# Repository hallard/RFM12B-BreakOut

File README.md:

RFM12B RFM69CW breakout board NRF24L01 socket
=============================================

This is a utility breakout board for connecting RFM12B or RFM69CW device onto 
NRF24L01 sockets

this breakout add the feature of one of : 
- **adding** Micro SD card connector (V1.1 only)
- **adding** SPI Flash EEProm
- **adding** Some Leds to see what's going on

The 1.2 version has been added to be smaller than the 1.1 version, to achieve this I needed 
to remove the SD Card holder, so if you want SD use version 1.1.

1.2 version comes in two versions, one with classic 2x4 PTH connector and the other with the same
but SMD version of the connector, this permit to have the PCB quite the same size of the original
RFM12B or RFM69CM module size.

This has been created to work with the [ArduiPi][4] Project, but this breakout
can be used anywhere where you use NRF24L01 or has NRF24L01 connector.

The same breakout board exists also for RFM69W and RFM69HW on this [repo][2]
 
ArduiPi project is a shield for Raspberry Pi that brings Arduino low level extended I/O to Raspberry Pi.

You can find information about this project and others on [ArduiPi Site][4] 

Check out news and other on my [blog][5]

Detailed Description
====================

Everything is documented on this dedicated [post][6]

# **Version 1.2**  

## Schematic  

## Boards  
&nbsp;
&nbsp;

# **Version 1.2 SMD connector**  

## Schematic  
  
## Boards  
&nbsp;
&nbsp;

# **Version 1.1 with SD Card**  

## Schematic  
  
## Boards  
&nbsp;
&nbsp;

[2]: [https://github.com/hallard/RFM69W-BreakOut]
[3]: http://hallard.me/rfm12b-breakout/ 
[4]: http://hallard.me/arduipi
[5]: http://hallard.me
[6]: http://hallard.me/rfm12b-breakout/

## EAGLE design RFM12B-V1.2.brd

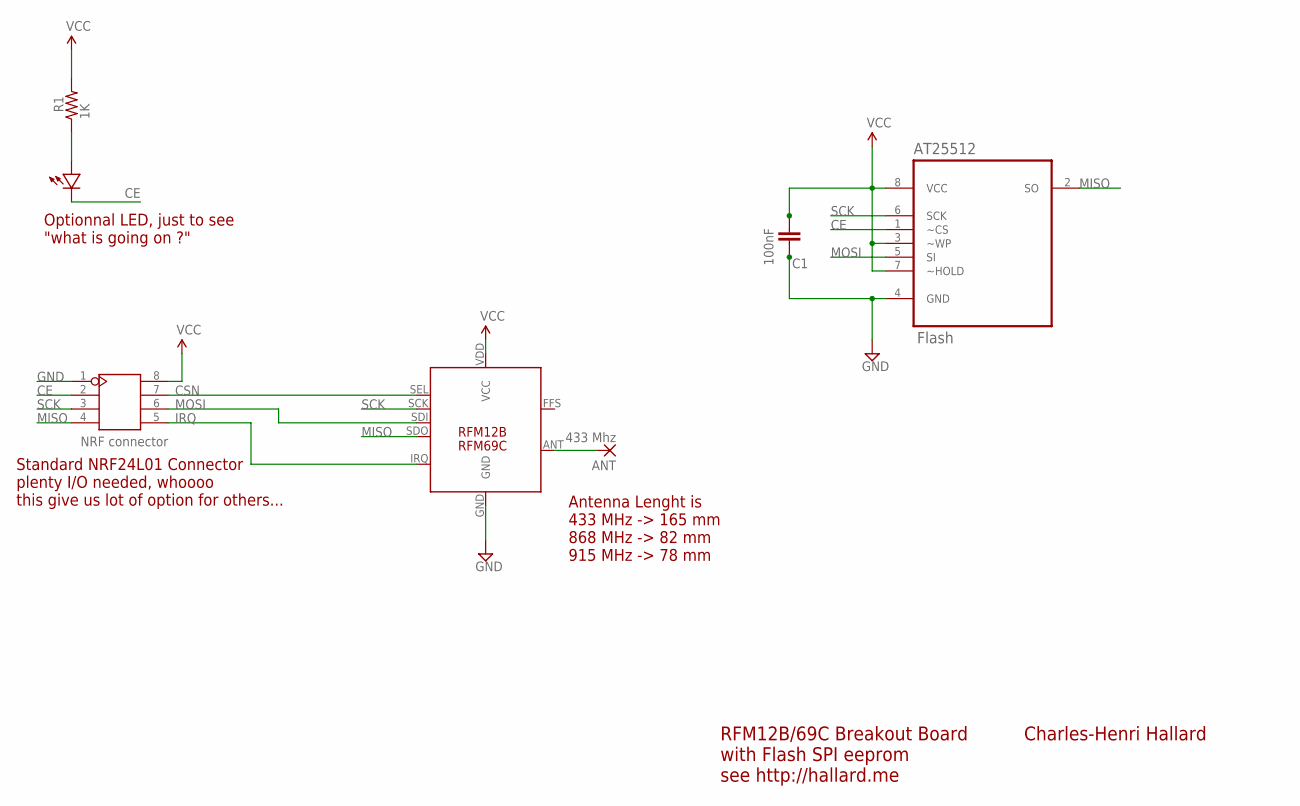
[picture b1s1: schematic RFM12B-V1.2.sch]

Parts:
ANT: 433 Mhz; 1,6/0,8
AT25512: Flash; SOIC127P600X175-8N
C1: 100nF; 0805-CAP
J1: NRF connector; 2X4P-2.54
R1: 1K; 0805-RES
U$1: LED0805-LARGE; 0805-LED-LARGEPADS
U$2: RFM12B

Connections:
CE: AT25512.1 (~CS), J1.2, U$1.MINUS
CSN: J1.7, U$2.SEL
GND: AT25512.4 (GND), C1.2, J1.1, U$2.GND
IRQ: J1.5, U$2.IRQ
MISO: AT25512.2 (SO), J1.4, U$2.SDO
MOSI: AT25512.5 (SI), J1.6, U$2.SDI
unnamed: ANT.1, U$2.ANT
unnamed: R1.1, U$1.PLUS
SCK: AT25512.6 (SCK), J1.3, U$2.SCK
VCC: AT25512.3 (~WP), AT25512.7 (~HOLD), AT25512.8 (VCC), C1.1, J1.8, R1.2, U$2.VDD (VCC)

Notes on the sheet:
RFM12B/69C Breakout Board with Flash SPI eeprom see http://hallard.me
Charles-Henri Hallard
Antenna Lenght is 433 MHz -> 165 mm 868 MHz -> 82 mm 915 MHz -> 78 mm
Optionnal LED, just to see "what is going on ?"
Standard NRF24L01 Connector plenty I/O needed, whoooo this give us lot of option for others...
RFM69C

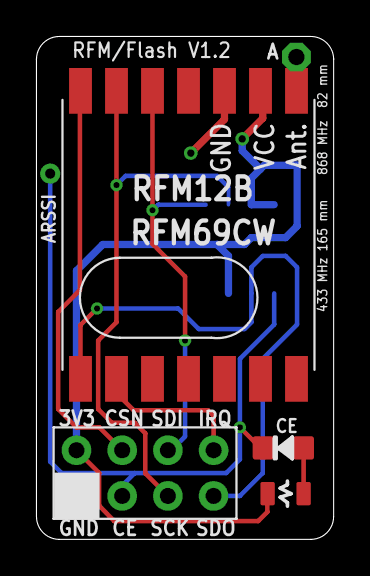
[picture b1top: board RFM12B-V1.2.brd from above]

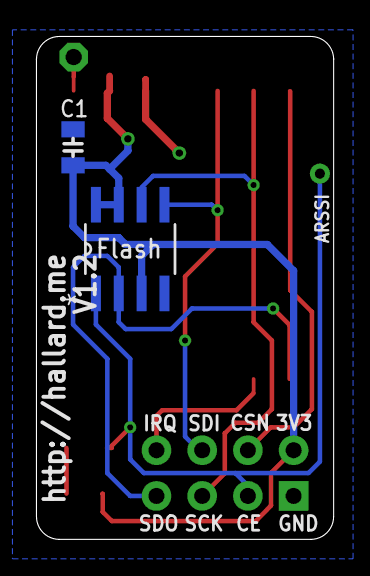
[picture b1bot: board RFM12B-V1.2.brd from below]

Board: 2 copper layers, 16.5 x 27.9 mm, 7 parts (2 on the bottom side), 10 nets.

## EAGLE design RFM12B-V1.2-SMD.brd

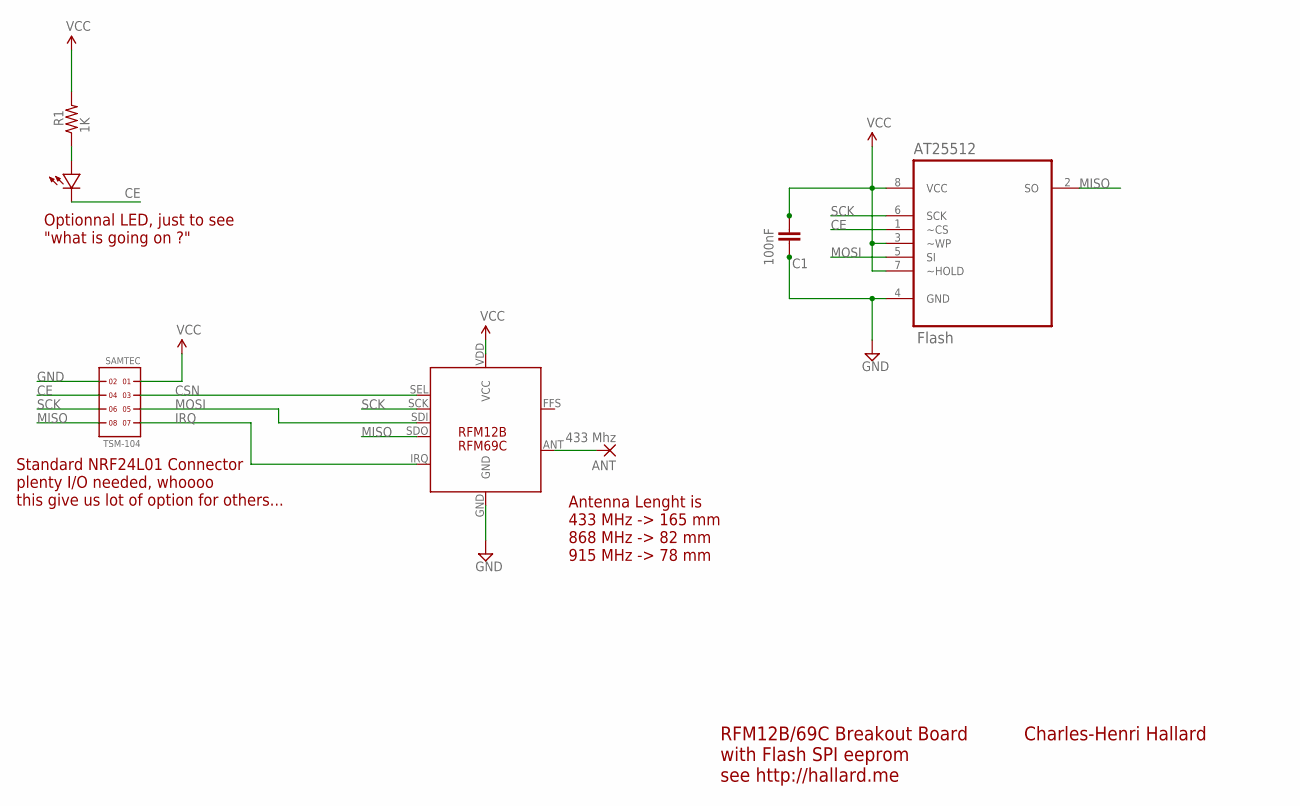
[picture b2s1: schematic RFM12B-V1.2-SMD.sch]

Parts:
ANT: 433 Mhz; 1,6/0,8
AT25512: Flash; SOIC127P600X175-8N
C1: 100nF; 0805-CAP
R1: 1K; 0805-RES
SAMTEC: TSM-104
U$2: RFM12B
U$3: LED0805-LARGE; 0805-LED-LARGEPADS

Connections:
CE: AT25512.1 (~CS), SAMTEC.4, U$3.MINUS
CSN: SAMTEC.3, U$2.SEL
GND: AT25512.4 (GND), C1.2, SAMTEC.2, U$2.GND
IRQ: SAMTEC.7, U$2.IRQ
MISO: AT25512.2 (SO), SAMTEC.8, U$2.SDO
MOSI: AT25512.5 (SI), SAMTEC.5, U$2.SDI
unnamed: ANT.1, U$2.ANT
unnamed: R1.1, U$3.PLUS
SCK: AT25512.6 (SCK), SAMTEC.6, U$2.SCK
VCC: AT25512.3 (~WP), AT25512.7 (~HOLD), AT25512.8 (VCC), C1.1, R1.2, SAMTEC.1, U$2.VDD (VCC)

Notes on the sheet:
RFM12B/69C Breakout Board with Flash SPI eeprom see http://hallard.me
Charles-Henri Hallard
Antenna Lenght is 433 MHz -> 165 mm 868 MHz -> 82 mm 915 MHz -> 78 mm
Optionnal LED, just to see "what is going on ?"
Standard NRF24L01 Connector plenty I/O needed, whoooo this give us lot of option for others...
RFM69C

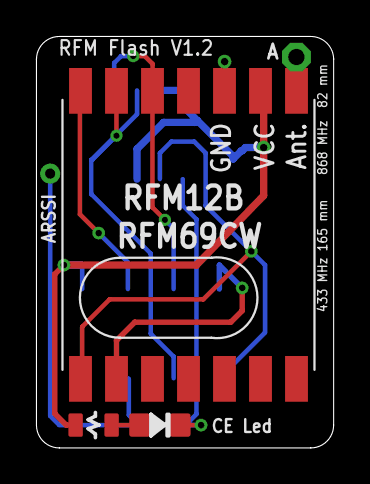
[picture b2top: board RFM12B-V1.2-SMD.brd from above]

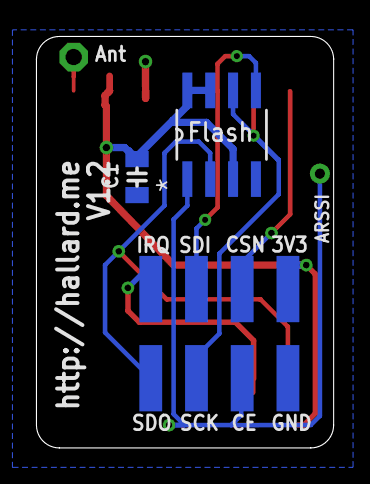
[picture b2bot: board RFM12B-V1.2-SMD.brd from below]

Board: 2 copper layers, 16.5 x 22.9 mm, 7 parts (3 on the bottom side), 10 nets.

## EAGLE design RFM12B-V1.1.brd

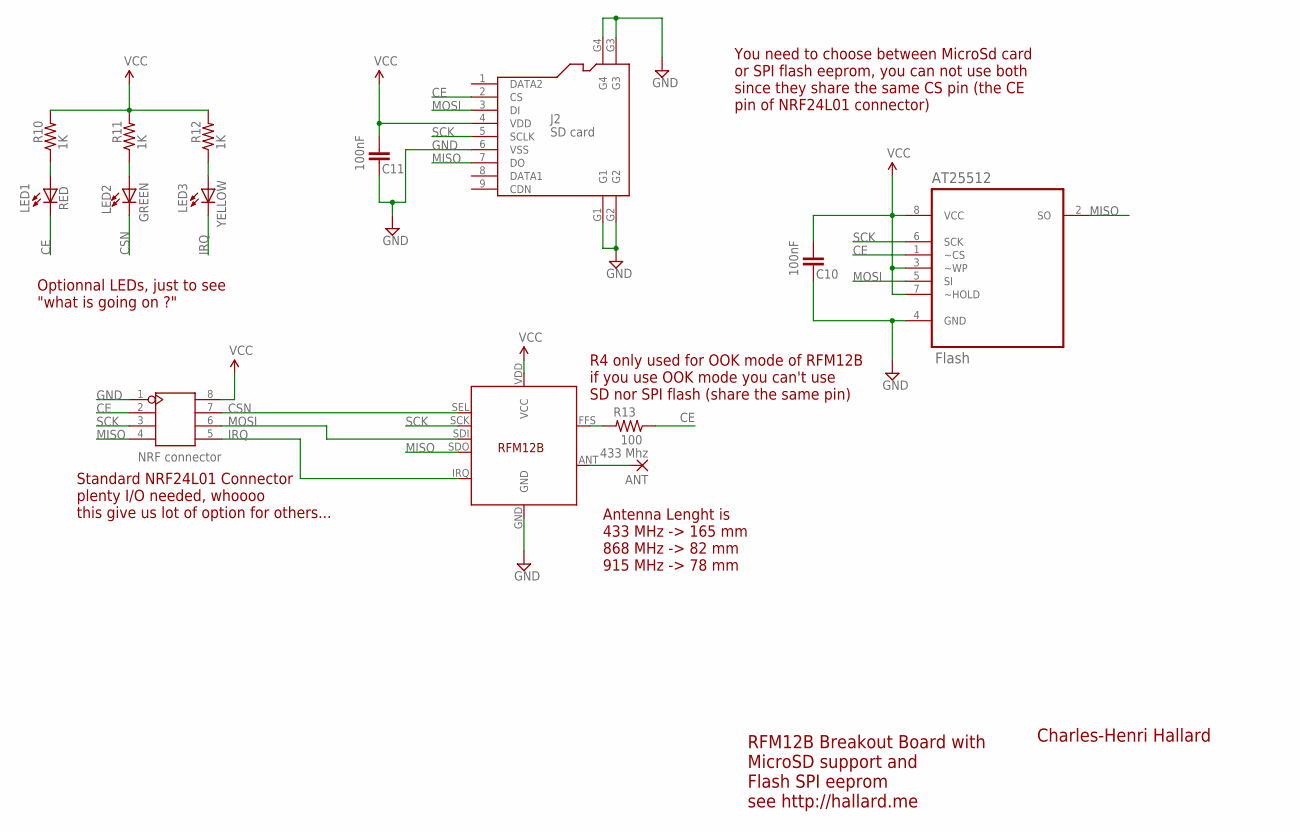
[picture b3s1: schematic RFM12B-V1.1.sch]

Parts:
ANT: 433 Mhz; 1,6/0,8
AT25512: Flash; SOIC127P600X175-8N
C10, C11: 100nF; C0805
J1: NRF connector; 2X4P-2.54
J2: SD card; 9P-SMD-W/-RING
LED1: RED; LED-805
LED2: GREEN; LED-805
LED3: YELLOW; LED-805
R10, R11, R12: 1K; M0805
R13: 100; M0805
U$2: RFM12B

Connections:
CE: AT25512.1 (~CS), J1.2, J2.2 (CS), LED1.C, R13.1
CSN: J1.7, LED2.C, U$2.SEL
GND: AT25512.4 (GND), C10.2, C11.2, J1.1, J2.6 (VSS), J2.G1, J2.G2, J2.G3, J2.G4, U$2.GND
IRQ: J1.5, LED3.C, U$2.IRQ
MISO: AT25512.2 (SO), J1.4, J2.7 (DO), U$2.SDO
MOSI: AT25512.5 (SI), J1.6, J2.3 (DI), U$2.SDI
unnamed: ANT.1, U$2.ANT
unnamed: LED1.A, R10.1
unnamed: LED2.A, R11.1
unnamed: LED3.A, R12.1
unnamed: R13.2, U$2.FFS
SCK: AT25512.6 (SCK), J1.3, J2.5 (SCLK), U$2.SCK
VCC: AT25512.3 (~WP), AT25512.7 (~HOLD), AT25512.8 (VCC), C10.1, C11.1, J1.8, J2.4 (VDD), R10.2, R11.2, R12.2, U$2.VDD (VCC)

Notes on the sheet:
RFM12B Breakout Board with MicroSD support and Flash SPI eeprom see http://hallard.me
Charles-Henri Hallard
Antenna Lenght is 433 MHz -> 165 mm 868 MHz -> 82 mm 915 MHz -> 78 mm
You need to choose between MicroSd card or SPI flash eeprom, you can not use both since they share the same CS pin (the CE pin of NRF24L01 connector)
Optionnal LEDs, just to see "what is going on ?"
Standard NRF24L01 Connector plenty I/O needed, whoooo this give us lot of option for others...
R4 only used for OOK mode of RFM12B if you use OOK mode you can't use SD nor SPI flash (share the same pin)

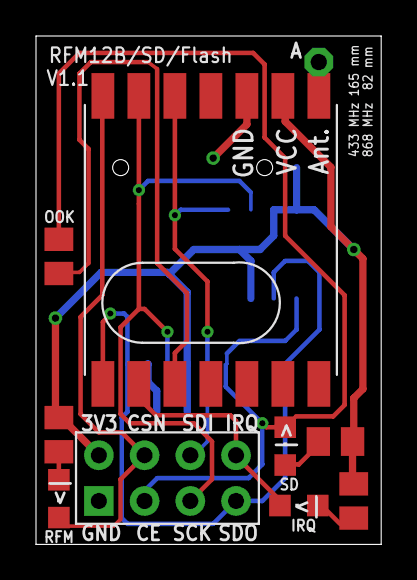
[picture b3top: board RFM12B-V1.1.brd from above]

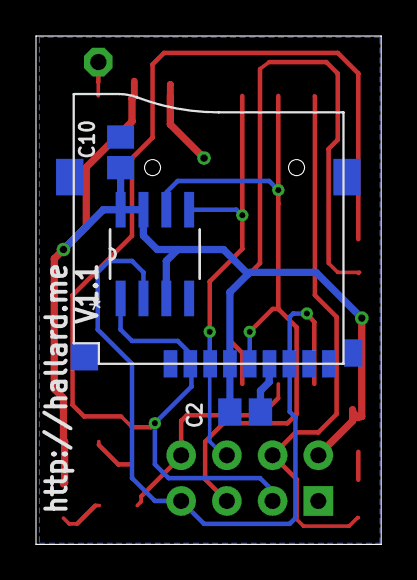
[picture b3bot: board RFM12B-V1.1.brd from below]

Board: 2 copper layers, 19.2 x 28.2 mm, 14 parts (4 on the bottom side), 13 nets.

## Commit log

2013-08-27 Initial Commit
    Initial Commit
2013-08-27 Bad link
    Bad link
2014-01-09 Version sent to OSH
    Latest revision sent to PCB fab
2014-01-21 Added Images
2014-01-21 Display images
2014-01-21 Layout style
2014-01-21 layout test
2014-01-21 Center Images
2014-01-21 Centering Image
2014-01-21 Centering Images
2014-01-21 Center Image
2014-01-21 Test Image
2014-01-21 Center
2014-01-21 Display format
2014-02-07 Removed Eagle Backup Files
2014-09-25 Added version 1.2 and 1.2 SMD
    Added smaller version 1.2 and ultra small 1.2 SMD
2014-09-25 Updated for V1.2
2014-09-25 Updated presentation
2014-09-25 Font Change
